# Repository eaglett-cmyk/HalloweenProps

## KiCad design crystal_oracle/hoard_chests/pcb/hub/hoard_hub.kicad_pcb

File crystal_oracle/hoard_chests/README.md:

# Hoard Chests — pop-open prize chests for the Crystal Oracle

Fifteen small treasure chests, five per prize tier (Silver Coin, Gold Star, Dragon Gem). When the
Oracle awards a tier, one loaded chest of that tier glows, unlatches and pops open. The grown-up
reloads and closes chests between groups; a closed lid tells the hub the chest is ready again.

**Status (2026-11-12): designed, nothing built or tested on hardware.** Print and wire ONE chest
and cycle it a couple of hundred times before printing fifteen. See "Not verified" at the end.

| Folder | What |
|---|---|
| `docs/DESIGN.md` | the contract: how a chest works, hub pins, link packets |
| `cad/hoard_chest.scad` + `cad/stl/` | parametric chest (small + long), latch arm, three emblems |
| `cad/hoard_hub_case.scad` + STLs | case for the hub board |
| `pcb/` | KiCad boards, Gerber zips, `PCB-NOTES.md` (netlist, how to order) |
| `firmware/hoard_hub/` | hub firmware (Arduino, ESP32) + its README (serial commands, calibration) |
| `docs/PARTS-RESEARCH.md` | parts list with part numbers and where to buy, verified dimensions |
| `docs/ORACLE-LINK.md` | how the show tells the hub (plinth relay, config key) |
| `docs/codex/` | Codex's critique of the concept |

## What to print (per chest)

| File | Qty | Filament | How |
|---|---|---|---|
| `chest_small_body.stl` or `chest_long_body.stl` | 1 | wood / stone colour | upright, no supports |
| `chest_small_lid.stl` or `chest_long_lid.stl` | 1 | same | as exported: flat top on the bed, no supports |
| `chest_small_deck.stl` or `chest_long_deck.stl` | 1 | same as the body, or black | as exported (top face on the bed) |
| `chest_backplate.stl` | 1 | same as the body | flat (same plate for both sizes) |
| `latch_arm.stl` | 1 | any PLA/PETG, 100 % infill | flat |
| `emblem_coin.stl` / `emblem_star.stl` / `emblem_gem.stl` | 1 | translucent (Starfrost / a clear gold / Dragonberry or red) | face up |

**What the kids see (2026-11-13):** the **deck** is a flush cover over the back compartment, so an
open chest shows only the prize bay and a plain shelf behind it. The servo, switch, node board and
wiring are underneath; only two narrow slots (for the lid's latch tongue and switch finger) and one
small hole (manual release) are left. The **backplate** closes the channel on the back that holds
the rubber band and the lid's tail. The pixel and its wires were already hidden (behind the emblem
and under the floor). Still in view from behind: the hinge and the patch cable, so stand the chests
with their backs to a wall or backdrop.

**Screws: #4 x 1/2" flat-head** (the ones bought for the Wakestone plinth cover) everywhere a
screw goes into printed plastic: 7 per chest (1 node board, 2 deck, 4 backplate) and 4 in the hub
case, so **109 for the full set of 15**. Pilot holes are 2.5 mm and deep enough for the full
1/2". The only other screws are the two tiny ones in each servo's bag (a #4 does not fit through
the servo's 2 mm tab holes).

Small = bay 110 x 58 x 40 mm (outside 114 x 86 x 62 with the lid). Long = bay 160 x 58 x 40 mm for
full-size bars (outside 164 x 86 x 62). Suggested set: 10 small (Silver, Gold) + 5 long (Gem).
0.2 mm layers, 3 walls, 15 % infill is plenty. Rough guess 70 to 90 g per small chest.

Change sizes in the `.scad` (`bay_w`, `bay_d`, `bay_h`) and re-export with
`openscad -o out.stl -D "part=\"body_print\"" -D "size=\"small\"" hoard_chest.scad`.
`part="check"` must stay (almost) empty: it tests every moving part against every fixed one.

**Measure your servo first.** The latch height depends on two SG90 numbers that vary between
makers: `sv_tab_z` (bottom of the body to the underside of the mounting tabs, drawn as 16.0) and
`sv_boss` (bottom of the body to the top of the round gear boss, drawn as 26.7). If yours differ by
more than 0.5 mm, change them and re-export the body.

## Parts per chest

SG90 servo, lever microswitch (Omron SS-01GL, or SS-5GL / KW12-3), one pre-wired WS2812B pixel
disc (10 mm) with its 10 cm lead, one Hoard Node board (RJ45, 3-pin header, 5-way screw terminal,
470 uF), one Ethernet patch cable, a #10 or #12 rubber band, a hinge pin (1.75 mm filament or a
straightened large paper clip, as long as the chest is wide), seven #4 x 1/2" flat-head screws, two
short wires for the switch. Full list with part numbers: `docs/PARTS-RESEARCH.md`.

## Assembling a chest

1. **Pixel**: push the pixel disc into the round cavity in the lock plate (LEDs facing out), feed
   its three input wires down the channel, along the groove under the floor and up through the
   hole into the back compartment. A dab of hot glue holds the disc; tape over the groove. Press
   the emblem cap into the cavity. (Long chest: the 10 cm lead is about 3 cm short. Splice on
   an extension.)
2. **Switch**: solder two wires to the switch's COM and NO lugs, drop the switch into its pocket
   against the partition, lever up.
3. **Node board**: wires into the screw terminal in this order from the back of the chest:
   `5V` (pixel +), `D` (pixel data in), `G` (pixel ground), `SW` and `G` (the two switch wires).
   Nose the RJ45 jack into the window in the back wall, lower the board onto its post, one #4 x 1/2" screw (stop when it is snug: the flat head bears on the board).
4. **Servo**: drop it between the two brackets, shaft end towards the node board
   (the shaft must line up with the slot block on the partition; the cable leaves under the bracket), two servo screws down through the
   tabs. Plug it into the 3-pin header: brown = GND, red = 5V, orange = signal.
5. **Arm**: do not fit it yet. Plug the chest into the hub, run `lock <port>` from the serial
   console so the servo sits at its lock position, then press the arm onto the spline pointing
   straight at the partition (tip in the slot) and fit the horn screw. `open <port>` must swing
   it a quarter turn clockwise (seen from above) to lie over the servo. Fine-tune with
   `cal <port> lock <us>` / `cal <port> open <us>`.
6. **Deck**: tuck the wires down, lay the deck in (countersinks up, the round hole over the horn
   screw, the notch round the slot block), two #4 x 1/2" screws into the corner bosses. Run
   `open` / `lock` once more: the arm must swing freely under it.
7. **Lid**: hold the lid in place, push the hinge pin through all the knuckles and the tail.
8. **Rubber band**: lark's-head the band through the hole in the lid's tail, hook the free loop
   into one of the two slanted slots in the fin on the back wall (lower slot = stronger). The lid
   must snap fully open and stay open. Then screw the backplate onto the two cheeks (four
   #4 x 1/2"). Take it off to remove the bands for storage.
9. Close the lid and hold it half a second: the latch turns, the emblem starts to breathe.

Manual release (dead servo, no power): small Phillips screwdriver through the hole in the back
slope of the lid (and the hole in the deck under it), onto the horn screw, a quarter turn clockwise.

## The hub

Build the board from `pcb/PCB-NOTES.md`, flash `firmware/hoard_hub` (see its README), 5 V 4 A
supply. Ports 1-5 Silver, 6-10 Gold, 11-15 Gem. **The patch cables are not Ethernet: never plug a
chest or the hub into a network port.** TEST button: short press = award the next tier, hold
2 s = open everything for reloading, hold 6 s = identify sweep. `arm confirm` on the serial console
makes closed chests wait for a TEST press before they count as loaded (stops kids re-arming
empty chests).

## Not verified

* Nothing has been printed, soldered, flashed or run. The firmware compiles; the boards pass
  KiCad's design-rule check; the CAD passes its own collision check. That is all.
* Latch height against a real SG90 (see "Measure your servo first"), the press fit of the arm on
  the spline (`spline_d`, 4.7 mm), the switch operating point (`sw_op`), the RJ45 window against
  the real jack, the deck's clearance over the arm and horn screw (0.8 mm drawn), and whether a #10/#12 band pops a loaded lid crisply.
* Pixel data and servo pulses through the multiplexers over 1 to 2 m of patch cable.
* The link from the show to the hub has only been tested against the fake plinth.

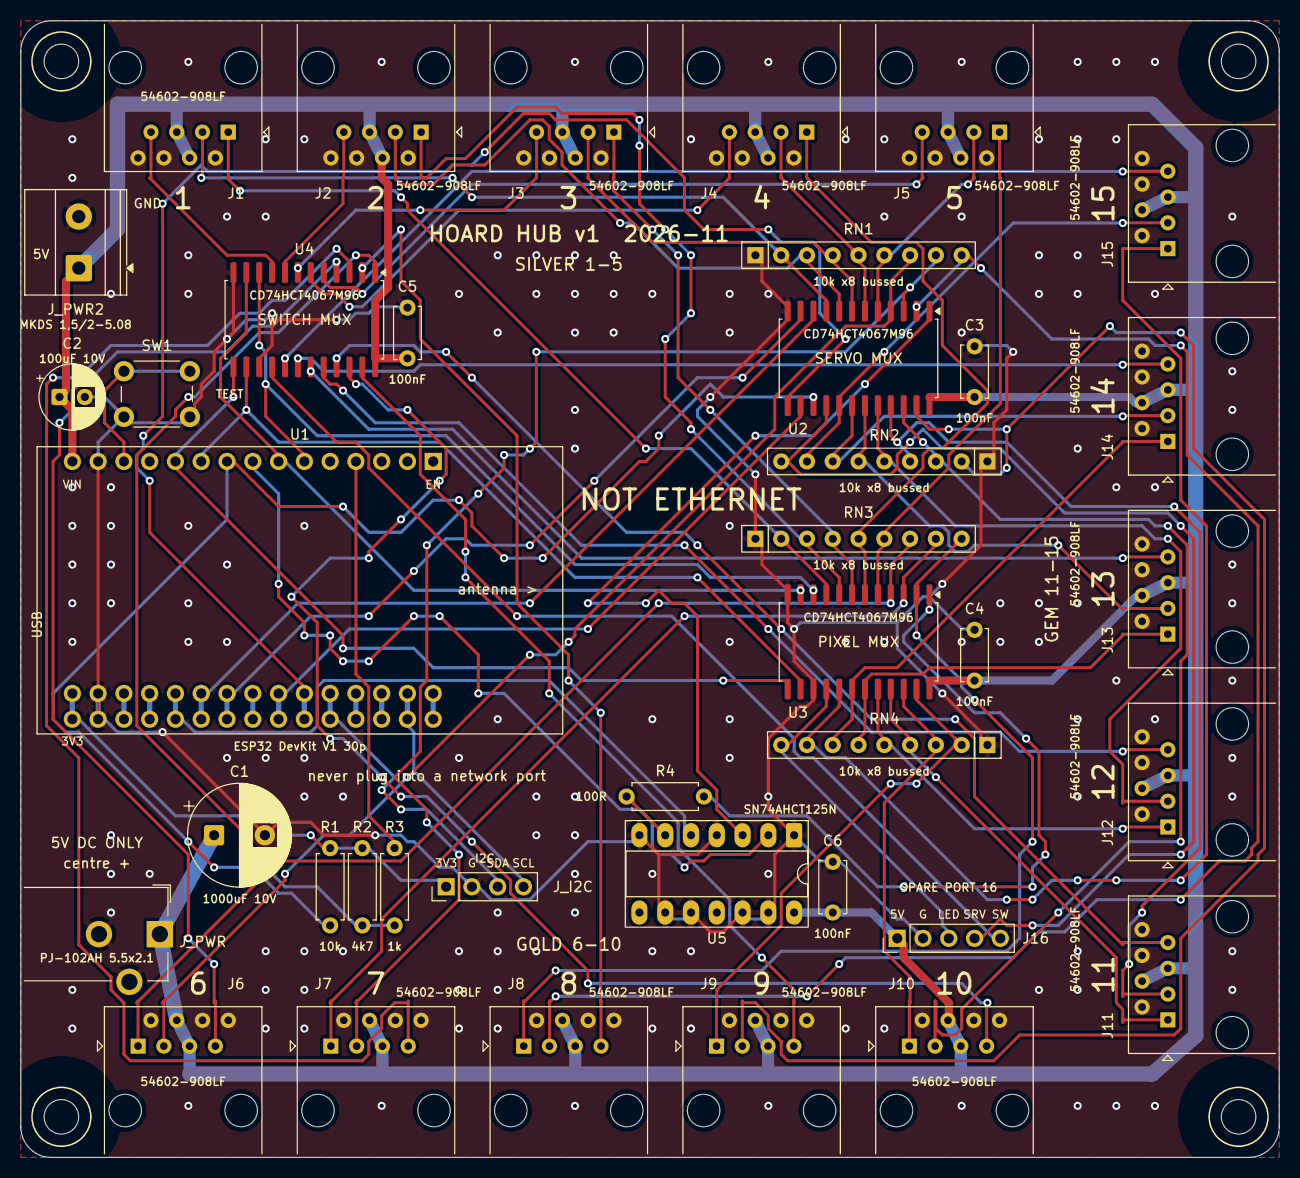
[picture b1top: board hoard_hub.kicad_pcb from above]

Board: 2 copper layers, 124.0 x 112.0 mm, 43 parts (0 on the bottom side), 70 nets.

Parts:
C1: 1000uF 10V; CP_Radial_D10.0mm_P5.00mm
C2: 100uF 10V; CP_Radial_D6.3mm_P2.50mm
C3, C4, C5, C6: 100nF; C_Disc_D5.0mm_W2.5mm_P5.00mm
H1, H2, H3, H4: M3 3.4mm NPTH; MountingHole_3.4mm_NPTH
J1, J2, J3, J4, J5, J6, J7, J8, J9, J10, J11, J12, J13, J14, J15: 54602-908LF; RJ45_Amphenol_54602-x08_Horizontal
J16: SPARE PORT 16; PinHeader_1x05_P2.54mm_Vertical
J_I2C: I2C; PinHeader_1x04_P2.54mm_Vertical
J_PWR: PJ-102AH 5.5x2.1; BarrelJack_CUI_PJ-102AH_Horizontal
J_PWR2: MKDS 1,5/2-5.08; TerminalBlock_Phoenix_MKDS-1,5-2-5.08_1x02_P5.08mm_Horizont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
R1: 10k; R_Axial_DIN0207_L6.3mm_D2.5mm_P7.62mm_Horizontal
R2: 4k7; R_Axial_DIN0207_L6.3mm_D2.5mm_P7.62mm_Horizontal
R3: 1k; R_Axial_DIN0207_L6.3mm_D2.5mm_P7.62mm_Horizontal
R4: 100R; R_Axial_DIN0207_L6.3mm_D2.5mm_P7.62mm_Horizontal
RN1, RN2, RN3, RN4: 10k x8 bussed; R_Array_SIP9
SW1: TEST; SW_PUSH_6mm
U1: ESP32 DevKit V1 30p; ESP32_DevKitV1_30pin_dual_width
U2, U3, U4: CD74HCT4067M96; SOIC-24W_7.5x15.4mm_P1.27mm
U5: SN74AHCT125N; DIP-14_W7.62mm_Socket_LongPads

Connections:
+3V3: J_I2C.1, R1.2, R2.2, U1.30
+5V: C1.1, C2.1, C3.1, C4.1, C5.1, C6.1, J1.4, J1.5, J2.4, J2.5, J3.4, J3.5, J4.4, J4.5, J5.4, J5.5, J6.4, J6.5, J7.4, J7.5, J8.4, J8.5, J9.4, J9.5, J10.4, J10.5, J11.4, J11.5, J12.4, J12.5, J13.4, J13.5, J14.4, J14.5, J15.4, J15.5, J16.1, J_PWR.1, J_PWR2.1, U1.15, U2.24, U3.24, U4.24, U5.14
GND: C1.2, C2.2, C3.2, C4.2, C5.2, C6.2, J1.2, J1.6, J1.8, J2.2, J2.6, J2.8, J3.2, J3.6, J3.8, J4.2, J4.6, J4.8, J5.2, J5.6, J5.8, J6.2, J6.6, J6.8, J7.2, J7.6, J7.8, J8.2, J8.6, J8.8, J9.2, J9.6, J9.8, J10.2, J10.6, J10.8, J11.2, J11.6, J11.8, J12.2, J12.6, J12.8, J13.2, J13.6, J13.8, J14.2, J14.6, J14.8, J15.2, J15.6, J15.8, J16.2, J_I2C.2, J_PWR.2, J_PWR.3, J_PWR2.2, RN1.1, RN2.1, RN3.1, RN4.1, SW1.2, U1.14, U1.29, U2.12, U3.12, U3.15, U4.12, U4.15, U5.1, U5.4, U5.7, U5.9, U5.10, U5.12, U5.13
GPIO4: U1.26, U5.5
GPIO13: SW1.1, U1.13
GPIO16: U1.25, U2.10
GPIO17: U1.24, U2.11
GPIO18: U1.22, U2.14
GPIO19: U1.21, U2.13
GPIO25: U1.8, U5.2
GPIO34: R3.2, U1.4
LED_1: J1.1, RN3.2, U3.9
LED_2: J2.1, RN3.3, U3.8
LED_3: J3.1, RN3.4, U3.7
LED_4: J4.1, RN3.5, U3.6
LED_5: J5.1, RN3.6, U3.5
LED_6: J6.1, RN3.7, U3.4
LED_7: J7.1, RN3.8, U3.3
LED_8: J8.1, RN3.9, U3.2
LED_9: J9.1, RN4.2, U3.23
LED_10: J10.1, RN4.3, U3.22
LED_11: J11.1, RN4.4, U3.21
LED_12: J12.1, RN4.5, U3.20
LED_13: J13.1, RN4.6, U3.19
LED_14: J14.1, RN4.7, U3.18
LED_15: J15.1, RN4.8, U3.17
LED_16: J16.3, RN4.9, U3.16
PIXEL_COM: R4.2, U3.1
PIXEL_RAW: R4.1, U5.6
SCAN0: U1.6, U3.10, U4.10
SCAN1: U1.7, U3.11, U4.11
SCAN2: U1.10, U3.14, U4.14
SCAN3: U1.11, U3.13, U4.13
SCL: J_I2C.4, U1.17
SDA: J_I2C.3, U1.20
SERVO_1: J1.3, RN1.2, U2.9
SERVO_2: J2.3, RN1.3, U2.8
SERVO_3: J3.3, RN1.4, U2.7
SERVO_4: J4.3, RN1.5, U2.6
SERVO_5: J5.3, RN1.6, U2.5
SERVO_5V: U2.1, U5.3
SERVO_6: J6.3, RN1.7, U2.4
SERVO_7: J7.3, RN1.8, U2.3
SERVO_8: J8.3, RN1.9, U2.2
SERVO_9: J9.3, RN2.2, U2.23
SERVO_10: J10.3, RN2.3, U2.22
SERVO_11: J11.3, RN2.4, U2.21
SERVO_12: J12.3, RN2.5, U2.20
SERVO_13: J13.3, RN2.6, U2.19
SERVO_14: J14.3, RN2.7, U2.18
SERVO_15: J15.3, RN2.8, U2.17
SERVO_16: J16.4, RN2.9, U2.16
SERVO_EN: R1.1, U1.9, U2.15
SW_1: J1.7, U4.9
SW_2: J2.7, U4.8
SW_3: J3.7, U4.7
SW_4: J4.7, U4.6
SW_5: J5.7, U4.5
SW_6: J6.7, U4.4
SW_7: J7.7, U4.3
SW_8: J8.7, U4.2
SW_9: J9.7, U4.23
SW_10: J10.7, U4.22
SW_11: J11.7, U4.21
SW_12: J12.7, U4.20
SW_13: J13.7, U4.19
SW_14: J14.7, U4.18
SW_15: J15.7, U4.17
SW_16: J16.5, U4.16
SW_COM: R2.1, R3.1, U4.1

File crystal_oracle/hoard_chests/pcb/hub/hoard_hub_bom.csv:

Comment,Designator,Footprint,Manufacturer Part Number
1000uF 10V,C1,CP_Radial_D10.0mm_P5.00mm,
100uF 10V,C2,CP_Radial_D6.3mm_P2.50mm,
100nF,"C3,C4,C5,C6",C_Disc_D5.0mm_W2.5mm_P5.00mm,
RJ45 8P8C horizontal THT,"J1,J10,J11,J12,J13,J14,J15,J2,J3,J4,J5,J6,J7,J8,J9",RJ45_Amphenol_54602-x08_Horizontal,54602-908LF
SPARE PORT 16,J16,PinHeader_1x05_P2.54mm_Vertical,
I2C,J_I2C,PinHeader_1x04_P2.54mm_Vertical,
DC barrel jack 5.5x2.1,J_PWR,BarrelJack_CUI_PJ-102AH_Horizontal,PJ-102AH
"MKDS 1,5/2-5.08",J_PWR2,"TerminalBlock_Phoenix_MKDS-1,5-2-5.08_1x02_P5.08mm_Horizontal",
10k,R1,R_Axial_DIN0207_L6.3mm_D2.5mm_P7.62mm_Horizontal,
4k7,R2,R_Axial_DIN0207_L6.3mm_D2.5mm_P7.62mm_Horizontal,
1k,R3,R_Axial_DIN0207_L6.3mm_D2.5mm_P7.62mm_Horizontal,
100R,R4,R_Axial_DIN0207_L6.3mm_D2.5mm_P7.62mm_Horizontal,
10k x8 bussed SIP-9,"RN1,RN2,RN3,RN4",R_Array_SIP9,4609X-101-103LF
TEST,SW1,SW_PUSH_6mm,
ESP32 DevKit V1 30p,U1,ESP32_DevKitV1_30pin_dual_width,
CD74HCT4067 SOIC-24W,"U2,U3,U4",SOIC-24W_7.5x15.4mm_P1.27mm,CD74HCT4067M96
SN74AHCT125N DIP-14,U5,DIP-14_W7.62mm_Socket_LongPads,SN74AHCT125N

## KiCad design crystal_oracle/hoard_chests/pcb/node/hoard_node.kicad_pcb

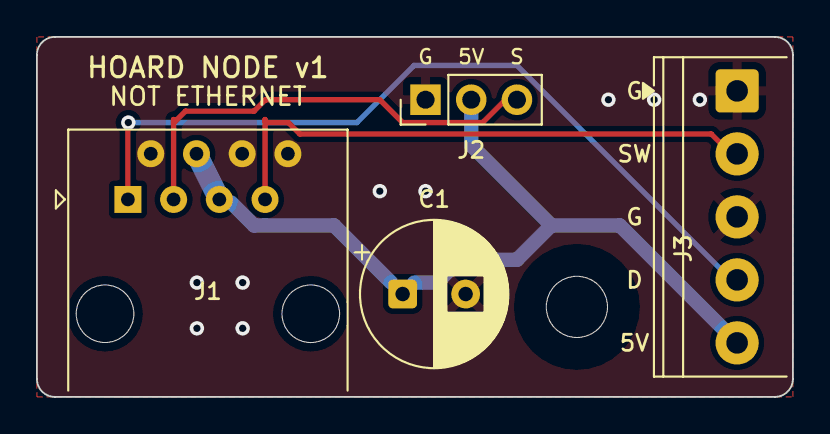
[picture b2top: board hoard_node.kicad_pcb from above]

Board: 2 copper layers, 42.0 x 20.0 mm, 5 parts (0 on the bottom side), 5 nets.

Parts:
C1: 470uF 10V; CP_Radial_D8.0mm_P3.50mm
H1: M3 3.4mm NPTH; MountingHole_3.4mm_NPTH
J1: 54602-908LF; RJ45_Amphenol_54602-x08_Horizontal
J2: SERVO; PinHeader_1x03_P2.54mm_Vertical
J3: PT 1,5/5-3,5-H; TerminalBlock_Phoenix_PT-1,5-5-3.5-H_1x05_P3.50mm_Horizontal

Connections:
+5V: C1.1, J1.4, J1.5, J2.2, J3.5
GND: C1.2, J1.2, J1.6, J1.8, J2.1, J3.1, J3.3
LED: J1.1, J3.4
SERVO: J1.3, J2.3
SW: J1.7, J3.2

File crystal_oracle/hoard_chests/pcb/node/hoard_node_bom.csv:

Comment,Designator,Footprint,Manufacturer Part Number
470uF 10V,C1,CP_Radial_D8.0mm_P3.50mm,
RJ45 8P8C horizontal THT,J1,RJ45_Amphenol_54602-x08_Horizontal,54602-908LF
SERVO,J2,PinHeader_1x03_P2.54mm_Vertical,
"PT 1,5/5-3,5-H",J3,"TerminalBlock_Phoenix_PT-1,5-5-3.5-H_1x05_P3.50mm_Horizontal",

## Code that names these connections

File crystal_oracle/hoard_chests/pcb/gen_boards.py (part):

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# ----------------------------------------------------------------------------- HUB
ESP_LEFT = ["EN", "VP", "VN", "IO34", "IO35", "IO32", "IO33", "IO25", "IO26", "IO27", "IO14", "IO12", "IO13", "GND", "VIN"]
ESP_RIGHT = ["IO23", "IO22", "TX0", "RX0", "IO21", "IO19", "IO18", "IO5", "IO17", "IO16", "IO4", "IO2", "IO15", "GND", "3V3"]
ESP_NET = {"VIN": "+5V", "GND": "GND", "3V3": "+3V3", "IO13": "GPIO13", "IO34": "GPIO34", "IO25": "GPIO25",
           "IO26": "SERVO_EN", "IO4": "GPIO4", "IO16": "GPIO16", "IO17": "GPIO17", "IO18": "GPIO18",
           "IO19": "GPIO19", "IO32": "SCAN0", "IO33": "SCAN1", "IO27": "SCAN2", "IO14": "SCAN3",
           "IO21": "SDA", "IO22": "SCL"}


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    # ---- multiplexers (SOIC-24W, top side) + their pull-down arrays and 100 nF
    so = ("Package_SO", "SOIC-24W_7.5x15.4mm_P1.27mm")
    D.place(*so, "U2", "CD74HCT4067M96", 82.55, 78.74, 270,
            mux_pins("SERVO_5V", ["GPIO16", "GPIO17", "GPIO18", "GPIO19"], "SERVO_EN", "SERVO", 16))
    D.place(*so, "U3", "CD74HCT4067M96", 82.55, 50.8, 270,
            mux_pins("PIXEL_COM", ["SCAN0", "SCAN1", "SCAN2", "SCAN3"], "GND", "LED", 16))
    D.place(*so, "U4", "CD74HCT4067M96", 27.94, 82.55, 270,
            mux_pins("SW_COM", ["SCAN0", "SCAN1", "SCAN2", "SCAN3"], "GND", "SW", 16))

    def rn(ref, x, y, rot, prefix, first):
        pins = {"1": "GND"}
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
    # ---- 74AHCT125 buffer
    D.place("Package_DIP", "DIP-14_W7.62mm_Socket_LongPads", "U5", "SN74AHCT125N", 76.2, 31.75, 270,
            {"1": "GND", "2": "GPIO25", "3": "SERVO_5V", "4": "GND", "5": "GPIO4", "6": "PIXEL_RAW", "7": "GND",
             "9": "GND", "10": "GND", "12": "GND", "13": "GND", "14": "+5V"})
    D.place(*cap, "C6", "100nF", 80.01, 24.13, 90, {"1": "+5V", "2": "GND"})
    ax = ("Resistor_THT", "R_Axial_DIN0207_L6.3mm_D2.5mm_P7.62mm_Horizontal")
    D.place(*ax, "R4", "100R", 59.69, 35.56, 0, {"1": "PIXEL_RAW", "2": "PIXEL_COM"})
    D.place(*ax, "R1", "10k", 30.48, 22.86, 90, {"1": "SERVO_EN", "2": "+3V3"})
    D.place(*ax, "R2", "4k7", 33.655, 22.86, 90, {"1": "SW_COM", "2": "+3V3"})
    D.place(*ax, "R3", "1k", 36.83, 22.86, 90, {"1": "SW_COM", "2": "GPIO34"})

    # ---- headers, button, VIN cap
    D.place("Connector_PinHeader_2.54mm", "PinHeader_1x05_P2.54mm_Vertical", "J16", "SPARE PORT 16",
            86.36, 21.59, 90, {"1": "+5V", "2": "GND", "3": "LED_16", "4": "SERVO_16", "5": "SW_16"})
    D.place("Connector_PinHeader_2.54mm", "PinHeader_1x04_P2.54mm_Vertical", "J_I2C", "I2C",
            41.91, 26.67, 90, {"1": "+3V3", "2": "GND", "3": "SDA", "4": "SCL"})
    D.place("Button_Switch_THT", "SW_PUSH_6mm", "SW1", "TEST", 10.16, 77.47, 0, {"1": "GPIO13", "2": "GND"})
    D.place("Capacitor_THT", "CP_Radial_D6.3mm_P2.50mm", "C2", "100uF 10V", 3.81, 74.93, 0, {"1": "+5V", "2": "GND"})

    # ---- route
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    jack_nets = []
    for n in list(range(1, 16)):
        jack_nets += ["SERVO_%d" % n, "LED_%d" % n, "SW_%d" % n]
    plan = (["+5V", "GND", "GPIO16", "GPIO17", "GPIO18", "GPIO19", "SCAN0", "SCAN1", "SCAN2", "SCAN3",
             "SERVO_EN", "GPIO25", "GPIO4", "SERVO_5V", "PIXEL_RAW", "PIXEL_COM", "SW_COM", "GPIO34",
             "+3V3", "SDA", "SCL", "GPIO13", "SERVO_16", "LED_16", "SW_16"] + jack_nets)
    failed = D.route_nets(plan, wide_nets=("+5V",), pre_gnd=pre_gnd)
    finish(D, failed, hub_silk)
    return D, failed
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            grid(range(56, 76, 2), [35.7]) + grid(range(14, 52, 2), [37.6]), size=1.0, required=False)
    D.label("5V DC ONLY", grid([7.5, 7.0, 8.0, 6.5], [31.0, 31.4, 32.0, 32.5]), size=1.0)
    D.label("centre +", grid([7.5, 7.0, 8.0, 6.5], [29.0, 29.5, 30]), size=1.0)
    D.label("SERVO MUX", [(82.55, 78.74), (82.55, 79.5)], size=1.0, required=False)
    D.label("PIXEL MUX", [(82.55, 50.8), (82.55, 51.5)], size=1.0, required=False)
    D.label("SWITCH MUX", [(27.94, 82.55), (27.94, 83.3)], size=1.0, required=False)
    D.label("5V", [(2.0, 89.0), (11.5, 88.9), (12.0, 88.9)], size=0.9, required=False)
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    nets = {"1": "LED", "2": "GND", "3": "SERVO", "4": "+5V", "5": "+5V", "6": "GND", "7": "SW", "8": "GND"}
    j1 = place_rj45(D, "J1", 'bottom', 9.5, nets)
    rj45_stubs(D, j1, nets, None)
    D.place("Connector_PinHeader_2.54mm", "PinHeader_1x03_P2.54mm_Vertical", "J2", "SERVO",
            21.59, 16.51, 90, {"1": "GND", "2": "+5V", "3": "SERVO"})
    # PT 1,5/5-3,5-H: wire entry faces +X; footprint pin numbers run top->bottom, so the nets are
    # assigned to give the order +5V, LED, GND, SW, GND from the back (y=0) edge.
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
